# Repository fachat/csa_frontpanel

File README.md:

# CS/A frontpanel design

This repo defines a front panel with toggle switches and push buttons to
read data from and write data to CS/A memory bus.

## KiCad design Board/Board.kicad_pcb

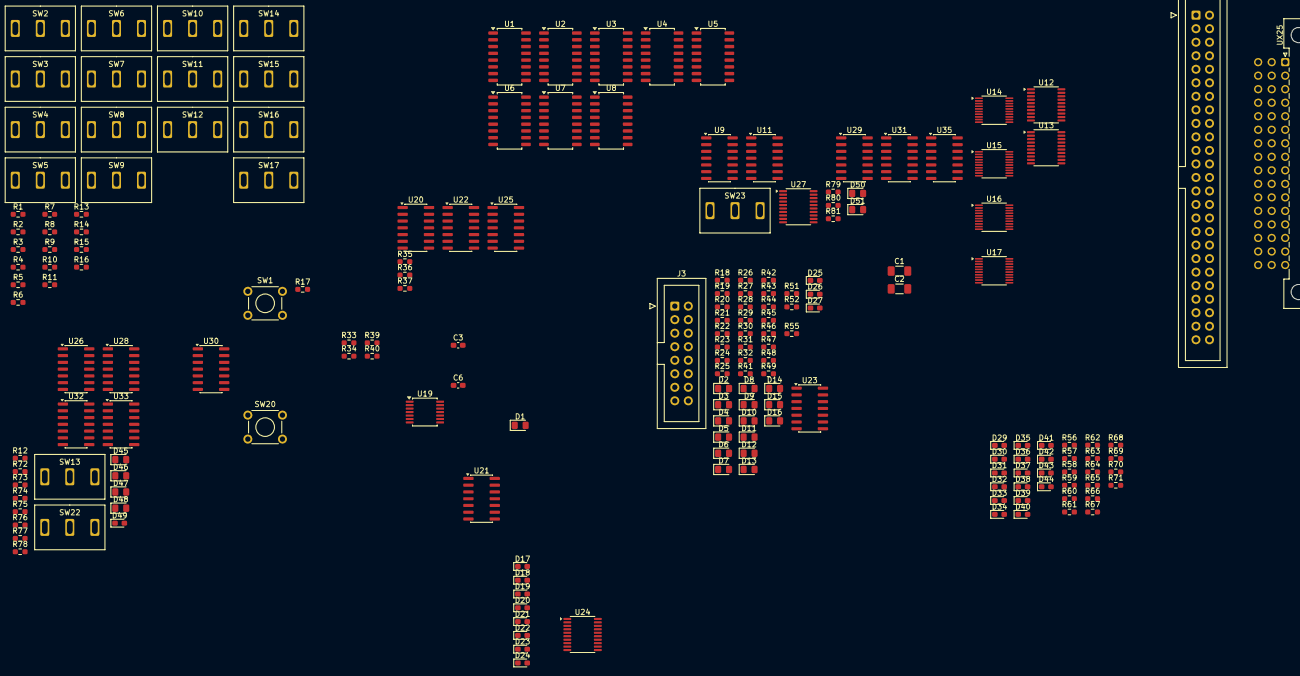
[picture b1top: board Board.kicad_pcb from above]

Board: 2 copper layers, 186 parts (0 on the bottom side), 260 nets, no tracks yet.

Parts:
C1, C2: 47u; C_1206_3216Metric_Pad1.33x1.80mm_HandSolder
C3, C6: 100n; C_0603_1608Metric_Pad1.08x0.95mm_HandSolder
D1, D2, D3, D4, D5, D6, D7, D8, D9, D10, D11, D12, D13, D14, D15, D16, D45, D46, D47, D48, D50, D51: LED; LED_0805_2012Metric_Pad1.15x1.40mm_HandSolder
D17, D18, D19, D20, D21, D22, D23, D24, D25, D26, D27, D29, D30, D31, D32, D33, D34, D35, D36, D37, D38, D39, D40, D41, D42, D43, D44, D49: LED; LED_0603_1608Metric_Pad1.05x0.95mm_HandSolder
J2: Conn_02x25_Odd_Even; IDC-Header_2x25_P2.54mm_Vertical
J3: Conn_02x08_Odd_Even; IDC-Header_2x08_P2.54mm_Vertical
R1, R2, R3, R4, R5, R6, R7, R8, R9, R10, R11, R12, R13, R14, R15, R16, R34, R35, R36, R37, R40, R49, R74, R77, R79: 10k; R_0603_1608Metric_Pad0.98x0.95mm_HandSolder
R17, R18, R19, R20, R21, R22, R23, R24, R25, R26, R27, R28, R29, R30, R31, R32, R41, R42, R43, R44, R45, R46, R47, R48, R51, R52, R55, R56, R57, R58, R59, R60, R61, R62, R63, R64, R65, R66, R67, R68, R69, R70, R71, R72, R73, R75, R76, R78, R80, R81: 560; R_0603_1608Metric_Pad0.98x0.95mm_HandSolder
R33, R39: 1k; R_0603_1608Metric_Pad0.98x0.95mm_HandSolder
SW1, SW20: SW_SPST; SW_TH_Tactile_Omron_B3F-107x
SW2, SW3, SW4, SW5, SW6, SW7, SW8, SW9, SW10, SW11, SW12, SW13, SW14, SW15, SW16, SW17, SW22, SW23: SW_SPDT; SW_K4625
U1, U2, U3, U4: 74LS257; SOP-16_4.4x10.4mm_P1.27mm
U5, U6, U7, U8: 74LS283; SOP-16_4.4x10.4mm_P1.27mm
U9: 74LS08; SOIC-14_3.9x8.7mm_P1.27mm
U11: 74LS32; SOIC-14_3.9x8.7mm_P1.27mm
U12, U13, U24, U27: 74LS273; TSSOP-20_4.4x6.5mm_P0.65mm
U14, U15, U16, U17: 74LS245; TSSOP-20_4.4x5mm_P0.5mm
U19: 74LS14; TSSOP-14_4.4x5mm_P0.65mm
U20: 74HCT00; SOIC-14_3.9x8.7mm_P1.27mm
U21, U22, U25: 74HCT74; SOIC-14_3.9x8.7mm_P1.27mm
U23: 74HCT02; SOIC-14_3.9x8.7mm_P1.27mm
U26, U28, U29, U30, U31, U32, U33, U35: 74LS06; SOIC-14_3.9x8.7mm_P1.27mm
UX25: CSASHORTBUSFA; DIN41612_C2_3x16_Male_Horizontal_THT

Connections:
A0: U5.5 (A1), U12.2 (Q0), U14.2 (A0), U31.5
A1: U5.3 (A2), U12.5 (Q1), U14.3 (A1), U31.9
A2: U5.14 (A3), U12.6 (Q2), U14.4 (A2), U31.11
A3: U5.12 (A4), U12.9 (Q3), U14.5 (A3), U31.13
A4: U6.5 (A1), U12.12 (Q4), U14.6 (A4), U32.1
A5: U6.3 (A2), U12.15 (Q5), U14.7 (A5), U32.3
A6: U6.14 (A3), U12.16 (Q6), U14.8 (A6), U32.5
A7: U6.12 (A4), U12.19 (Q7), U14.9 (A7), U32.9
A8: U7.5 (A1), U13.2 (Q0), U15.2 (A0), U32.11
A9: U7.3 (A2), U13.5 (Q1), U15.3 (A1), U32.13
A10: U7.14 (A3), U13.6 (Q2), U15.4 (A2), U33.1
A11: U7.12 (A4), U13.9 (Q3), U15.5 (A3), U33.3
A12: U8.5 (A1), U13.12 (Q4), U15.6 (A4), U33.5
A13: U8.3 (A2), U13.15 (Q5), U15.7 (A5), U33.9
A14: U8.14 (A3), U13.16 (Q6), U15.8 (A6), U33.11
A15: U8.12 (A4), U13.19 (Q7), U15.9 (A7), U33.13
A16: D13.2 (A), R13.1, SW14.2 (B), U16.2 (A0)
A17: D14.2 (A), R14.1, SW15.2 (B), U16.3 (A1)
A18: D15.2 (A), R15.1, SW16.2 (B), U16.4 (A2)
A19: D16.2 (A), R16.1, SW17.2 (B), U16.5 (A3)
ACTIVE: U9.4, U22.9 (Q), U35.5
B2PHI2: J2.48, UX25.c15 (2PHI2)
B8PHI2: J2.47, UX25.b16 (8PHI2)
BA0: J2.33, U14.18 (B0), UX25.c11 (A0)
BA1: J2.29, U14.17 (B1), UX25.b10 (A1)
BA2: J2.30, U14.16 (B2), UX25.c10 (A2)
BA3: J2.26, U14.15 (B3), UX25.b9 (A3)
BA4: J2.27, U14.14 (B4), UX25.c9 (A4)
BA5: J2.23, U14.13 (B5), UX25.b8 (A5)
BA6: J2.24, U14.12 (B6), UX25.c8 (A6)
BA7: J2.20, U14.11 (B7), UX25.b7 (A7)
BA8: J2.21, U15.18 (B0), UX25.c7 (A8)
BA9: J2.17, U15.17 (B1), UX25.b6 (A9)
BA10: J2.18, U15.16 (B2), UX25.c6 (A10)
BA11: J2.14, U15.15 (B3), UX25.b5 (A11)
BA12: J2.15, U15.14 (B4), UX25.c5 (A12)
BA13: J2.11, U15.13 (B5), UX25.b4 (A13)
BA14: J2.12, U15.12 (B6), UX25.c4 (A14)
BA15: J2.9, U15.11 (B7), UX25.b3 (A15)
BA16: J2.8, U16.18 (B0), UX25.c3 (A16)
BA17: J2.5, U16.17 (B1), UX25.b2 (A17)
BA18: J2.6, U16.16 (B2), UX25.c2 (A18)
BA19: J2.3, U16.15 (B3), UX25.b1 (A19)
BD0: J2.34, U17.18 (B0), U24.3 (D0), UX25.a12 (D0)
BD1: J2.31, U17.17 (B1), U24.4 (D1), UX25.a11 (D1)
BD2: J2.28, U17.16 (B2), U24.7 (D2), UX25.a10 (D2)
BD3: J2.25, U17.15 (B3), U24.8 (D3), UX25.a9 (D3)
BD4: J2.22, U17.14 (B4), U24.13 (D4), UX25.a8 (D4)
BD5: J2.19, U17.13 (B5), U24.14 (D5), UX25.a7 (D5)
BD6: J2.16, U17.12 (B6), U24.17 (D6), UX25.a6 (D6)
BD7: J2.13, U17.11 (B7), U24.18 (D7), UX25.a5 (D7)
BPHI1: J2.39, UX25.c13 (PHI1)
BPHI2: J2.42, U19.3, UX25.c12 (PHI2)
BRDY: J2.38, U19.5, U35.4, UX25.b13 (RDY)
BR/-W: J2.35, U16.14 (B4), UX25.b12 (R/-W)
BSYNC: J2.32, UX25.b11 (SYNC)
BV33: C2.1, J2.41, J3.7, UX25.b14 (VCC33)
CLKD: U19.8, U19.11, U22.3 (C)
CLKIN: J3.3, R39.1, SW13.2 (B), SW20.2 (B)
CLK_H: U13.11 (Cp), U23.10
CLK_L: U12.11 (Cp), U23.4
CLK_RD: U9.9, U11.1, U11.10, U20.5, U20.13, U22.8 (~Q), U23.12, U27.11 (Cp)
D0IN: J3.2, R1.2, SW2.2 (B), U1.2 (I0a), U3.2 (I0a), U17.2 (A0), U28.11
D1IN: J3.4, R2.1, SW3.2 (B), U1.5 (I0b), U3.5 (I0b), U17.3 (A1), U28.1
D2IN: J3.6, R3.1, SW4.2 (B), U1.14 (I0c), U3.14 (I0c), U17.4 (A2), U28.3
D3IN: J3.8, R4.1, SW5.2 (B), U1.11 (I0d), U3.11 (I0d), U17.5 (A3), U28.5
D4IN: J3.10, R5.1, SW6.2 (B), U2.2 (I0a), U4.2 (I0a), U17.6 (A4), U28.9
D5IN: J3.12, R6.1, SW7.2 (B), U2.5 (I0b), U4.5 (I0b), U17.7 (A5), U28.13
D6IN: J3.14, R7.1, SW8.2 (B), U2.14 (I0c), U4.14 (I0c), U17.8 (A6), U29.11
D7IN: J3.16, R8.1, SW9.2 (B), U2.11 (I0d), U4.11 (I0d), U17.9 (A7), U29.1
DIN0: U27.2 (Q0), U30.1
DIN1: U27.5 (Q1), U30.3
DIN2: U27.6 (Q2), U30.5
DIN3: U27.9 (Q3), U30.9
DIN4: U27.12 (Q4), U30.11
DIN5: U27.15 (Q5), U30.13
DIN6: U27.16 (Q6), U31.1
DIN7: U27.19 (Q7), U31.3
EFFRDY: U9.10, U20.3, U23.11
GND: C1.2, C2.2, C3.2, C6.2, J2.1, J2.49, J3.15, R9.2, R10.2, R11.2, R13.2, R14.2, R15.2, R16.2, R25.2, R26.2, R27.2, R28.2, R29.2, R30.2, R31.2, R32.2, R72.2, R73.2, R74.2, R75.2, R76.2, R77.2, R79.2, R80.2, R81.2, SW1.1 (A), SW2.3 (C), SW3.3 (C), SW4.3 (C), SW5.3 (C), SW6.3 (C), SW7.3 (C), SW8.3 (C), SW9.3 (C), SW13.1 (A), SW20.1 (A), U1.8 (GND), U1.15 (OE), U2.8 (GND), U2.15 (OE), U3.8 (GND), U3.15 (OE), U4.8 (GND), U4.15 (OE), U5.2 (B2), U5.6 (B1), U5.8 (GND), U5.11 (B4), U5.15 (B3), U6.2 (B2), U6.6 (B1), U6.8 (GND), U6.11 (B4), U6.15 (B3), U7.2 (B2), U7.6 (B1), U7.8 (GND), U7.11 (B4), U7.15 (B3), U8.2 (B2), U8.6 (B1), U8.8 (GND), U8.11 (B4), U8.15 (B3), U9.7 (GND), U11.7 (GND), U12.10 (GND), U13.10 (GND), U14.10 (GND), U15.10 (GND), U16.10 (GND), U17.10 (GND), U19.7 (GND), U20.7 (GND), U21.7 (GND), U22.7 (GND), U23.7 (GND), U24.10 (GND), U25.7 (GND), U26.7 (GND), U27.10 (GND), U28.7 (GND), U29.7 (GND), U30.7 (GND), U31.7 (GND), U32.7 (GND), U33.7 (GND), U35.7 (GND), UX25.a1 (GND), UX25.a16 (GND2)
INC: D9.2 (A), R9.1, SW10.2 (B), U5.7 (C0), U29.5
unnamed: C3.1, R33.2, R34.2, U19.1
unnamed: C6.1, R39.2, R40.2, U19.9
unnamed: D1.2 (A), R17.1
unnamed: D1.1 (K), U28.10
unnamed: D2.2 (A), R18.1
unnamed: D2.1 (K), U28.2
unnamed: D3.2 (A), R19.1
unnamed: D3.1 (K), U28.4
unnamed: D4.2 (A), R20.1
unnamed: D4.1 (K), U28.6
unnamed: D5.2 (A), R21.1
unnamed: D5.1 (K), U28.8
unnamed: D6.2 (A), R22.1
unnamed: D6.1 (K), U28.12
unnamed: D7.2 (A), R23.1
unnamed: D7.1 (K), U29.10
unnamed: D8.2 (A), R24.1
unnamed: D8.1 (K), U29.2
unnamed: D9.1 (K), R25.1
unnamed: D10.1 (K), R26.1
unnamed: D11.1 (K), R27.1
unnamed: D12.1 (K), R28.1
unnamed: D13.1 (K), R29.1
unnamed: D14.1 (K), R30.1
unnamed: D15.1 (K), R31.1
unnamed: D16.1 (K), R32.1
unnamed: D17.2 (A), R55.1
unnamed: D17.1 (K), U31.4
unnamed: D18.2 (A), R41.1
unnamed: D18.1 (K), U31.2
unnamed: D19.2 (A), R42.1
unnamed: D19.1 (K), U30.12
unnamed: D20.2 (A), R43.1
unnamed: D20.1 (K), U30.10
unnamed: D21.2 (A), R44.1
unnamed: D21.1 (K), U30.8
unnamed: D22.2 (A), R45.1
unnamed: D22.1 (K), U30.6
unnamed: D23.2 (A), R46.1
unnamed: D23.1 (K), U30.4
unnamed: D24.2 (A), R47.1
unnamed: D24.1 (K), U30.2
unnamed: D25.1 (K), R51.2
unnamed: D26.1 (K), R52.2
unnamed: D27.1 (K), R48.2
unnamed: D29.2 (A), R56.1
unnamed: D29.1 (K), U33.12
unnamed: D30.2 (A), R57.1
unnamed: D30.1 (K), U33.10
unnamed: D31.2 (A), R58.1
unnamed: D31.1 (K), U33.8
unnamed: D32.2 (A), R59.1
unnamed: D32.1 (K), U33.6
unnamed: D33.2 (A), R60.1
unnamed: D33.1 (K), U33.4
unnamed: D34.2 (A), R61.1
unnamed: D34.1 (K), U33.2
unnamed: D35.2 (A), R62.1
unnamed: D35.1 (K), U32.12
unnamed: D36.2 (A), R63.1
unnamed: D36.1 (K), U32.10
unnamed: D37.2 (A), R64.1
unnamed: D37.1 (K), U32.8
unnamed: D38.2 (A), R65.1
unnamed: D38.1 (K), U32.6
unnamed: D39.2 (A), R66.1
unnamed: D39.1 (K), U32.4
unnamed: D40.2 (A), R67.1
unnamed: D40.1 (K), U32.2
unnamed: D41.2 (A), R68.1
unnamed: D41.1 (K), U31.12
unnamed: D42.2 (A), R69.1
unnamed: D42.1 (K), U31.10
unnamed: D43.2 (A), R70.1
unnamed: D43.1 (K), U31.8
unnamed: D44.2 (A), R71.1
unnamed: D44.1 (K), U31.6
unnamed: D45.2 (A), U29.6
unnamed: D45.1 (K), R72.1
unnamed: D46.2 (A), U29.8
unnamed: D46.1 (K), R73.1
unnamed: D47.1 (K), R75.1
unnamed: D48.2 (A), U29.12
unnamed: D48.1 (K), R76.1
unnamed: D49.1 (K), R78.2
unnamed: D50.1 (K), R80.1
unnamed: D51.2 (A), U35.2
unnamed: D51.1 (K), R81.1
unnamed: R35.2, U9.5, U35.8
unnamed: R48.1, U26.12
unnamed: R51.1, U26.8
unnamed: R52.1, U26.6
unnamed: R78.1, U26.10
unnamed: U1.3 (I1a), U5.4 (S1)
unnamed: U1.6 (I1b), U5.1 (S2)
unnamed: U1.13 (I1c), U5.13 (S3)
unnamed: U1.10 (I1d), U5.10 (S4)
unnamed: U1.4 (Za), U12.3 (D0)
unnamed: U1.7 (Zb), U12.4 (D1)
unnamed: U1.12 (Zc), U12.7 (D2)
unnamed: U1.9 (Zd), U12.8 (D3)
unnamed: U2.3 (I1a), U6.4 (S1)
unnamed: U2.6 (I1b), U6.1 (S2)
unnamed: U2.13 (I1c), U6.13 (S3)
unnamed: U2.10 (I1d), U6.10 (S4)
unnamed: U3.3 (I1a), U7.4 (S1)
unnamed: U3.6 (I1b), U7.1 (S2)
unnamed: U3.13 (I1c), U7.13 (S3)
unnamed: U3.10 (I1d), U7.10 (S4)
unnamed: U4.3 (I1a), U8.4 (S1)
unnamed: U4.6 (I1b), U8.1 (S2)
unnamed: U4.13 (I1c), U8.13 (S3)
unnamed: U4.10 (I1d), U8.10 (S4)
unnamed: U5.9 (C4), U6.7 (C0)
unnamed: U6.9 (C4), U7.7 (C0)
unnamed: U7.9 (C4), U8.7 (C0)
unnamed: U9.8, U9.13
unnamed: U9.11, U11.4
unnamed: U11.5, U23.13
unnamed: U9.2, U11.6
unnamed: U11.8, U23.3
unnamed: U2.4 (Za), U12.13 (D4)
unnamed: U2.7 (Zb), U12.14 (D5)
unnamed: U2.12 (Zc), U12.17 (D6)
unnamed: U2.9 (Zd), U12.18 (D7)
unnamed: U3.4 (Za), U13.3 (D0)
unnamed: U3.7 (Zb), U13.4 (D1)
unnamed: U3.12 (Zc), U13.7 (D2)
unnamed: U3.9 (Zd), U13.8 (D3)
unnamed: U4.4 (Za), U13.13 (D4)
unnamed: U4.7 (Zb), U13.14 (D5)
unnamed: U4.12 (Zc), U13.17 (D6)
unnamed: U4.9 (Zd), U13.18 (D7)
unnamed: R77.1, U16.9 (A7)
unnamed: U19.6, U20.1
unnamed: U20.4, U20.8
unnamed: U11.9, U19.10, U21.3 (C), U21.11 (C)
unnamed: R37.2, U11.12, U11.13, U21.2 (D), U21.4 (~S), U21.10 (~S), U22.4 (~S), U26.1
unnamed: U21.5 (Q), U21.12 (D), U26.9
unnamed: U21.6 (~Q), U23.5, U26.5
unnamed: U21.9 (Q), U22.2 (D), U26.13
unnamed: U21.8 (~Q), U23.2, U23.8, U26.11
unnamed: U19.4, U19.13, U22.11 (C)
unnamed: U9.3, U22.12 (D)
unnamed: R36.2, U22.10 (~S), U22.13 (~R), U25.1 (~R), U25.4 (~S), U25.10 (~S)
unnamed: U23.1, U23.6, U23.9
unnamed: U24.2 (Q0), U27.3 (D0)
unnamed: U24.5 (Q1), U27.4 (D1)
unnamed: U24.6 (Q2), U27.7 (D2)
unnamed: U24.9 (Q3), U27.8 (D3)
unnamed: U24.12 (Q4), U27.13 (D4)
unnamed: U24.15 (Q5), U27.14 (D5)
unnamed: U24.16 (Q6), U27.17 (D6)
unnamed: U24.19 (Q7), U27.18 (D7)
unnamed: U19.12, U25.3 (C), U25.11 (C)
unnamed: U9.1, U25.5 (Q)
unnamed: U20.6, U25.12 (D)
unnamed: U20.9, U20.12, U25.9 (Q)
unnamed: U9.6, U35.3
RES: U19.2, U26.3
SEL: U1.1 (S), U2.1 (S), U3.1 (S), U4.1 (S), U20.10, U22.5 (Q), U25.2 (D)
SINGLE: D47.2 (A), R74.1, SW22.2 (B), U25.13 (~R), U29.13
UPET: D50.2 (A), R79.1, SW23.2 (B), U20.2, U35.1, U35.9
VBUF: J2.46, UX25.b15 (VBUF)
VCC: C1.1, D25.2 (A), D26.2 (A), D27.2 (A), D49.2 (A), J2.2, J2.50, J3.1, R1.1, R2.2, R3.2, R4.2, R5.2, R6.2, R7.2, R8.2, R12.1, R17.2, R18.2, R19.2, R20.2, R21.2, R22.2, R23.2, R24.2, R34.1, R35.1, R36.1, R37.1, R40.1, R41.2, R42.2, R43.2, R44.2, R45.2, R46.2, R47.2, R49.1, R55.2, R56.2, R57.2, R58.2, R59.2, R60.2, R61.2, R62.2, R63.2, R64.2, R65.2, R66.2, R67.2, R68.2, R69.2, R70.2, R71.2, SW10.1 (A), SW11.1 (A), SW12.1 (A), SW14.1 (A), SW15.1 (A), SW16.1 (A), SW17.1 (A), SW22.1 (A), SW23.1 (A), U1.16 (VCC), U2.16 (VCC), U3.16 (VCC), U4.16 (VCC), U5.16 (VCC), U6.16 (VCC), U7.16 (VCC), U8.16 (VCC), U9.14 (VCC), U11.14 (VCC), U12.20 (VCC), U13.20 (VCC), U14.1 (A->B), U14.20 (VCC), U15.1 (A->B), U15.20 (VCC), U16.1 (A->B), U16.20 (VCC), U17.1 (A->B), U17.20 (VCC), U19.14 (VCC), U20.14 (VCC), U21.14 (VCC), U22.14 (VCC), U23.14 (VCC), U24.20 (VCC), U25.14 (VCC), U26.14 (VCC), U27.20 (VCC), U28.14 (VCC), U29.14 (VCC), U30.14 (VCC), U31.14 (VCC), U32.14 (VCC), U33.14 (VCC), U35.14 (VCC), UX25.c1 (VCC), UX25.c16 (VCC2)
/ADDREN: U14.19 (CE), U15.19 (CE), U16.19 (CE)
/BBE: J2.10, U35.6, UX25.a4 (/BE)
/BIOSEL: J2.7, U16.12 (B6), UX25.a3 (/IOSEL)
/BIRQ: J2.40, UX25.a14 (/IRQ)
/BMEMSEL: J2.4, U16.13 (B5), UX25.a2 (/MEMSEL)
/BNMI: J2.37, UX25.a13 (/NMI)
/BRES: J2.43, UX25.a15 (/RES)
/DOUTEN: U11.3, U17.19 (CE)
/IO: D12.2 (A), R12.2, U16.8 (A6), U29.4
/MEM: D11.2 (A), R11.1, SW12.2 (B), U16.7 (A5), U29.3
/RES: R49.2, U12.1 (~Mr), U13.1 (~Mr), U21.1 (~R), U21.13 (~R), U22.1 (~R), U24.1 (~Mr), U26.4, U27.1 (~Mr)
/RESIN: J3.5, R33.1, SW1.2 (B)
/STOP: U9.12, U25.8 (~Q)
/WRITE: D10.2 (A), R10.1, SW11.2 (B), U11.2, U16.6 (A4), U29.9
